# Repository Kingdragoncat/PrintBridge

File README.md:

# PrintBridge

Im so done with needing to unplug all my cords and plug it all in ontip of a file of boxes to print one god damn thing so i made my wired printer wireless

## what is this thing

A small, cheap PCB that turns a wired USB printer into a WiFi network printer. It plugs into the printer's USB port as a USB **Host**, and exposes it on the network via raw JetDirect (port 9100) printing — works natively with macOS/Windows/Linux print dialogs, no drivers needed on the printer side.

Print jobs get spooled to the onboard micro SD card first, so if your wifi drops mid-print the job is safe and keeps going. because my wifi used to be *that* bad.

## pcb layout

## schematic

## specs

- ESP32-S3-WROOM-1 module — WiFi + native USB Host on one chip
- USB-A host port to connect to the printer
- USB-C for power input (5V only, no data)
- Micro SD card slot for print job spooling
- WS2812B addressable RGB status LED
- BOOT and RESET tactile switches
- 1x4 UART header for firmware flashing (with an external USB-serial adapter)
- AMS1117-3.3 voltage regulator with polyfuse protection
- FCC/CE modular certification inherited from the WROOM-1 module
- Board size: ~55 x 28mm

## how it works

1. plug PrintBridge into your printer's USB port
2. power it with any USB-C charger
3. it connects to your WiFi and starts listening on port 9100
4. add it as a network printer on your computer (raw/JetDirect protocol)
5. print! the job gets spooled to the SD card first, then fed to the printer

## wiring

**USB-C power in (J2):** 5V power only, no data lines connected. CC1/CC2 have 5.1k pull-downs so any USB-C charger recognizes it as a power sink. goes through a polyfuse for overcurrent protection, then into the AMS1117-3.3 regulator.

**USB-A host (USB1):** D+ and D- are wired to the ESP32-S3's USB PHY (GPIO19/GPIO20). VBUS gets raw 5V from the power rail — host mode has to supply power to the printer.

**SD card (J1):** SPI connection to the ESP32-S3 for spooling print data before sending to the printer.

**Status LED (D1):** WS2812B addressable LED. blue=booting, yellow=connecting, green=ready, cyan=receiving, purple=printing, red=error.

**Flashing:** no onboard USB-serial chip to keep costs down. use an external ~$3 USB-to-UART dongle on the 4-pin UART header (J3: 3V3/GND/TX/RX).

## BOM

every part has an LCSC part number and link so anyone can source and build this.

| Ref | Qty | Value | LCSC # | Package | Description | Unit Price | Subtotal | Link |
|-----|-----|-------|--------|---------|-------------|------------|----------|------|
| U1 | 1 | ESP32-S3-WROOM-1-N8 | C2913198 | Module | ESP32-S3 WiFi/BLE module (8MB flash) | $2.88 | $2.88 | [LCSC](https://www.lcsc.com/product-detail/C2913198.html) |
| USB1 | 1 | USB-A-F-90 | C168708 | Through-hole | USB-A host receptacle (to printer) | $0.15 | $0.15 | [LCSC](https://www.lcsc.com/product-detail/C168708.html) |
| J2 | 1 | TYPE-C-31-M-12 | C165948 | SMD | USB-C power input | $0.10 | $0.10 | [LCSC](https://www.lcsc.com/product-detail/C165948.html) |
| U2 | 1 | AMS1117-3.3 | C6186 | SOT-223 | 3.3V linear regulator | $0.05 | $0.05 | [LCSC](https://www.lcsc.com/product-detail/C6186.html) |
| SW1, SW2 | 2 | TS-1187A-B-A-B | C318884 | SMD | Tactile switches (BOOT + RESET) | $0.02 | $0.04 | [LCSC](https://www.lcsc.com/product-detail/C318884.html) |
| J1 | 1 | DM3AT-SF-PEJM5 | C114218 | SMD | Micro SD card connector | $0.65 | $0.65 | [LCSC](https://www.lcsc.com/product-detail/C114218.html) |
| D1 | 1 | WS2812B | C2761795 | 5050 | Addressable RGB status LED | $0.08 | $0.08 | [LCSC](https://www.lcsc.com/product-detail/C2761795.html) |
| R1, R2 | 2 | 10k | C269742 | 0805 | Pull-up resistors (EN + BOOT) | $0.01 | $0.02 | [LCSC](https://www.lcsc.com/product-detail/C269742.html) |
| R3, R4 | 2 | 5.1k | C269748 | 0805 | USB-C CC pull-down resistors | $0.01 | $0.02 | [LCSC](https://www.lcsc.com/product-detail/C269748.html) |
| C1, C3 | 2 | 100nF | C38141 | 0805 | Decoupling capacitors | $0.01 | $0.02 | [LCSC](https://www.lcsc.com/product-detail/C38141.html) |
| C2 | 1 | 10uF | C92341 | 0805 | Bulk capacitor (3V3 rail) | $0.02 | $0.02 | [LCSC](https://www.lcsc.com/product-detail/C92341.html) |
| C4 | 1 | 10uF | C92341 | 0805 | Bulk capacitor (SD card) | $0.02 | $0.02 | [LCSC](https://www.lcsc.com/product-detail/C92341.html) |
| F1 | 1 | Polyfuse 500mA | C106264 | 1206 | PTC resettable fuse | $0.07 | $0.07 | [LCSC](https://www.lcsc.com/product-detail/C106264.html) |
| J3 | 1 | Conn_01x04 | — | 2.54mm | UART pin header (for flashing) | $0.05 | $0.05 | [LCSC](https://www.lcsc.com/search?q=1x4+2.54mm+pin+header) |

**total: 18 parts — ~$4.17**

## firmware

the firmware is in the `software/` folder. its a PlatformIO project (Arduino framework). wifi, SD spooling, and the TCP print server are working. USB host printer driver is WIP.

see [software/README.md](software/README.md) for build and flash instructions.

## references

- [Espressif KiCad Libraries](https://github.com/espressif/kicad-libraries) — official symbols, footprints, 3D models
- [ESP32S3_PrintServer](https://github.com/MAXXTANG/ESP32S3_PrintServer) — reference firmware for ESP32-S3 print bridge
- [EspUsbHost](https://github.com/tanakamasayuki/EspUsbHost) — Arduino USB Host library for ESP32-S3

## license

do whatever you want with it honestly

---

made by Jonah Novoseller (Kingdragoncat)

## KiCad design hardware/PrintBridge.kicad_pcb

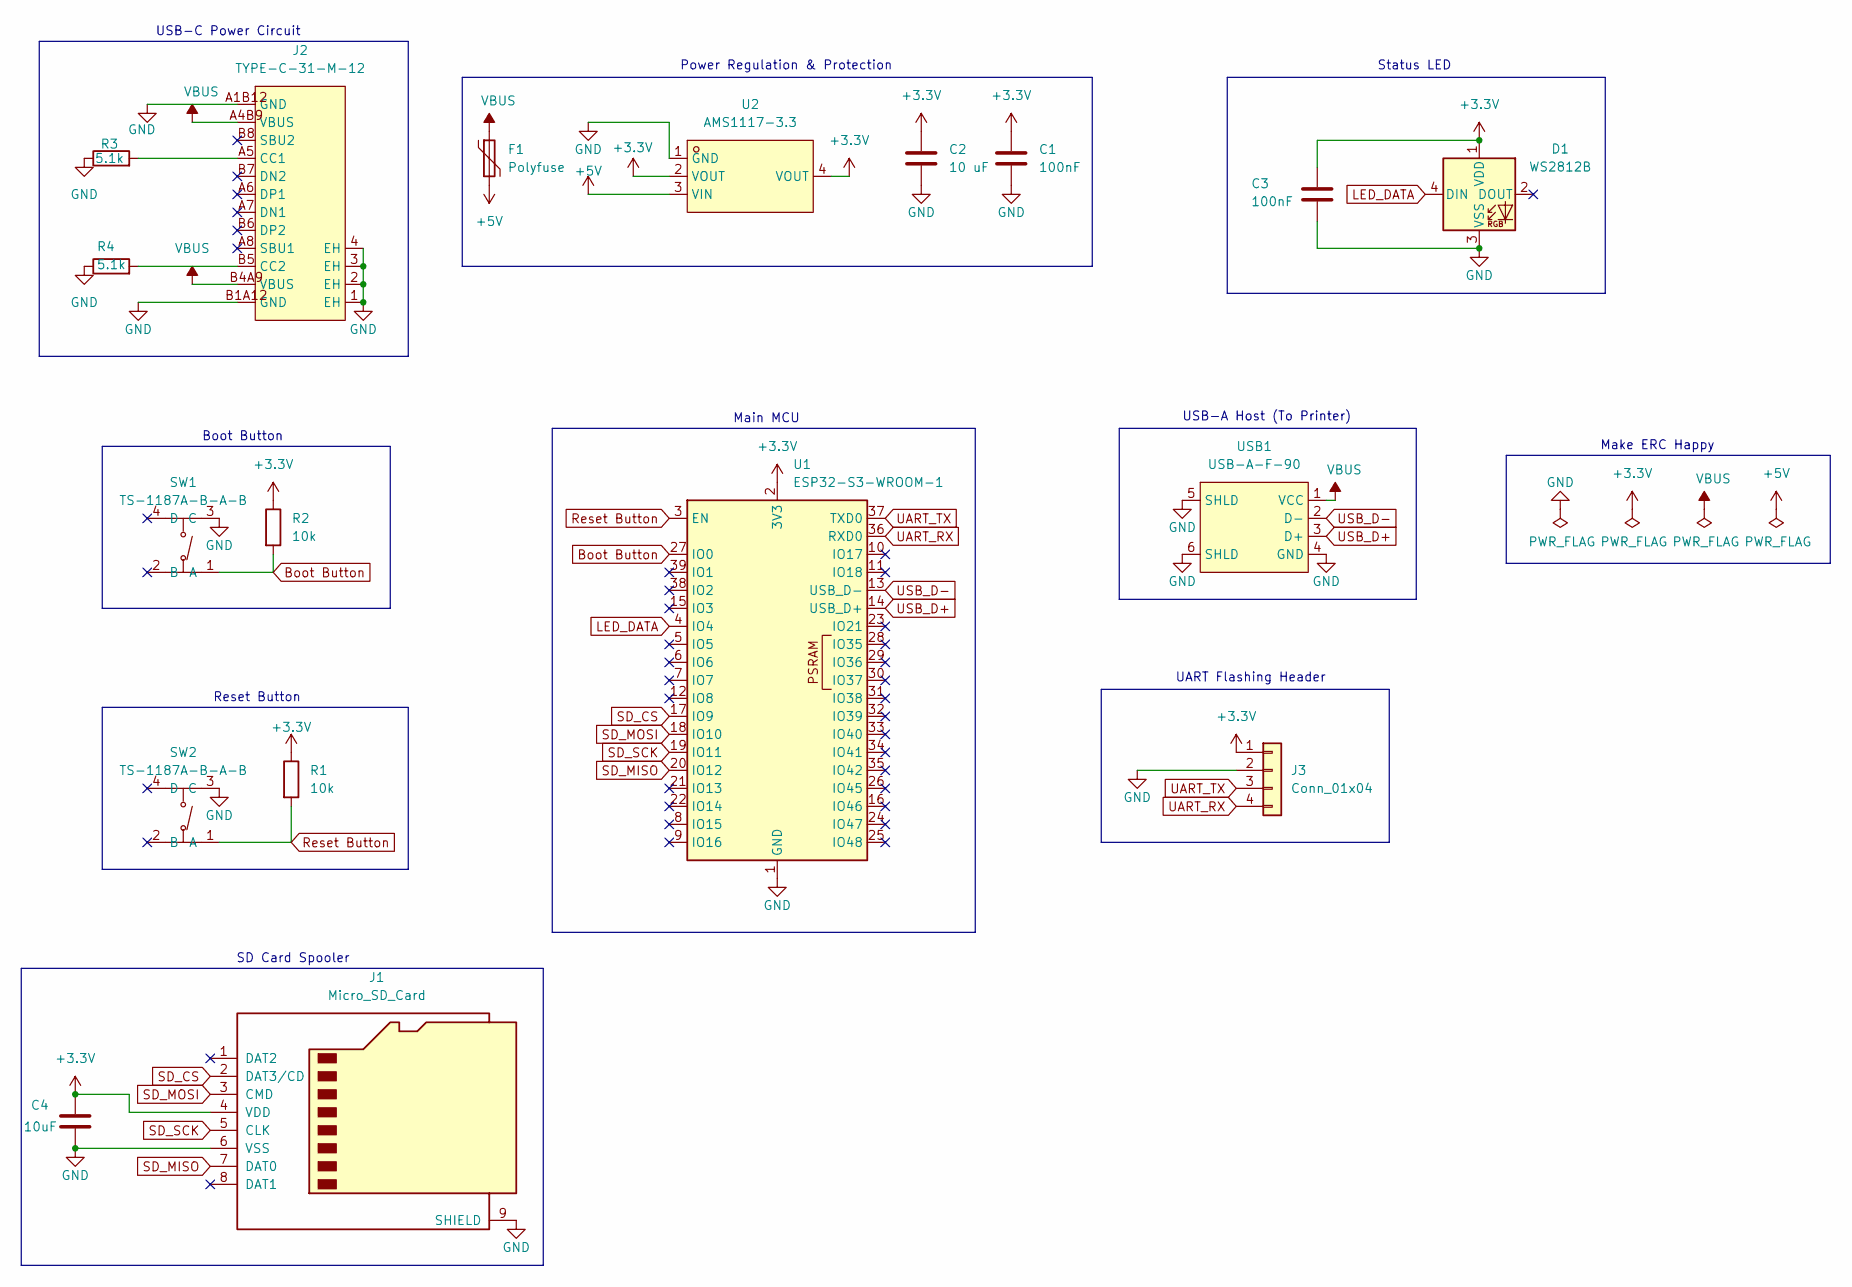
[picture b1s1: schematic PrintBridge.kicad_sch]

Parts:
C1, C3: 100nF; C_0805_2012Metric_Pad1.18x1.45mm_HandSolder
C2: 10 uF; C_0805_2012Metric_Pad1.18x1.45mm_HandSolder
C4: 10uF; C_0805_2012Metric_Pad1.18x1.45mm_HandSolder
D1: WS2812B; LED_WS2812B_PLCC4_5.0x5.0mm_P3.2mm
F1: Polyfuse; Fuse_1206_3216Metric_Pad1.42x1.75mm_HandSolder
J1: Micro_SD_Card; microSD_HC_Hirose_DM3AT-SF-PEJM5
J2: TYPE-C-31-M-12; USB-C_SMD-TYPE-C-31-M-12_1; MPN TYPE-C-31-M-12; LCSC Part C165948
J3: Conn_01x04; PinSocket_1x04_P2.54mm_Vertical
R1, R2: 10k; R_0805_2012Metric_Pad1.20x1.40mm_HandSolder
R3, R4: 5.1k; R_0805_2012Metric_Pad1.20x1.40mm_HandSolder
SW1, SW2: TS-1187A-B-A-B; SW-SMD_4P-L5.1-W5.1-P3.70-LS6.5-TL_H1.5; MPN TS-1187A-B-A-B; LCSC Part C318884
U1: ESP32-S3-WROOM-1
U2: AMS1117-3.3; SOT-223-3_L6.5-W3.4-P2.30-LS7.0-BR; MPN AMS1117-3.3; LCSC Part C6186
USB1: USB-A-F-90; USB-A-TH_C168708; MPN A/F90度外扣铜壳鱼叉脚无卷边加高9.3白胶PBT 不耐高温; LCSC Part C168708

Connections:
+3.3V: C1.1, C2.1, C3.1, C4.1, D1.1 (VDD), J1.4 (VDD), J3.1, R1.1, R2.1, U1.2 (3V3), U2.2 (VOUT), U2.4 (VOUT)
+5V: F1.2, U2.3 (VIN)
Boot Button: R2.2, SW1.1 (A), U1.27 (IO0)
GND: C1.2, C2.2, C3.2, C4.2, D1.3 (VSS), J1.6 (VSS), J1.9 (SHIELD), J2.1 (EH), J2.2 (EH), J2.3 (EH), J2.4 (EH), J2.A1B12 (GND), J2.B1A12 (GND), J3.2, R3.1, R4.1, SW1.3 (C), SW2.3 (C), U1.1 (GND), U1.40 (GND), U1.41 (GND), U2.1 (GND), USB1.4 (GND), USB1.5 (SHLD), USB1.6 (SHLD)
LED_DATA: D1.4 (DIN), U1.4 (IO4)
unnamed: J2.A5 (CC1), R3.2
unnamed: J2.B5 (CC2), R4.2
Reset Button: R1.2, SW2.1 (A), U1.3 (EN)
SD_CS: J1.2 (DAT3/CD), U1.17 (IO9)
SD_MISO: J1.7 (DAT0), U1.20 (IO12)
SD_MOSI: J1.3 (CMD), U1.18 (IO10)
SD_SCK: J1.5 (CLK), U1.19 (IO11)
UART_RX: J3.4, U1.36 (RXD0)
UART_TX: J3.3, U1.37 (TXD0)
USB_D+: U1.14 (USB_D+), USB1.3 (D+)
USB_D-: U1.13 (USB_D-), USB1.2 (D-)
VBUS: F1.1, J2.A4B9 (VBUS), J2.B4A9 (VBUS), USB1.1 (VCC)

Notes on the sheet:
Reset Button
UART Flashing Header
Boot Button
SD Card Spooler
Main MCU
Power Regulation & Protection
Status LED
USB-A Host (To Printer)
Make ERC Happy
USB-C Power Circuit

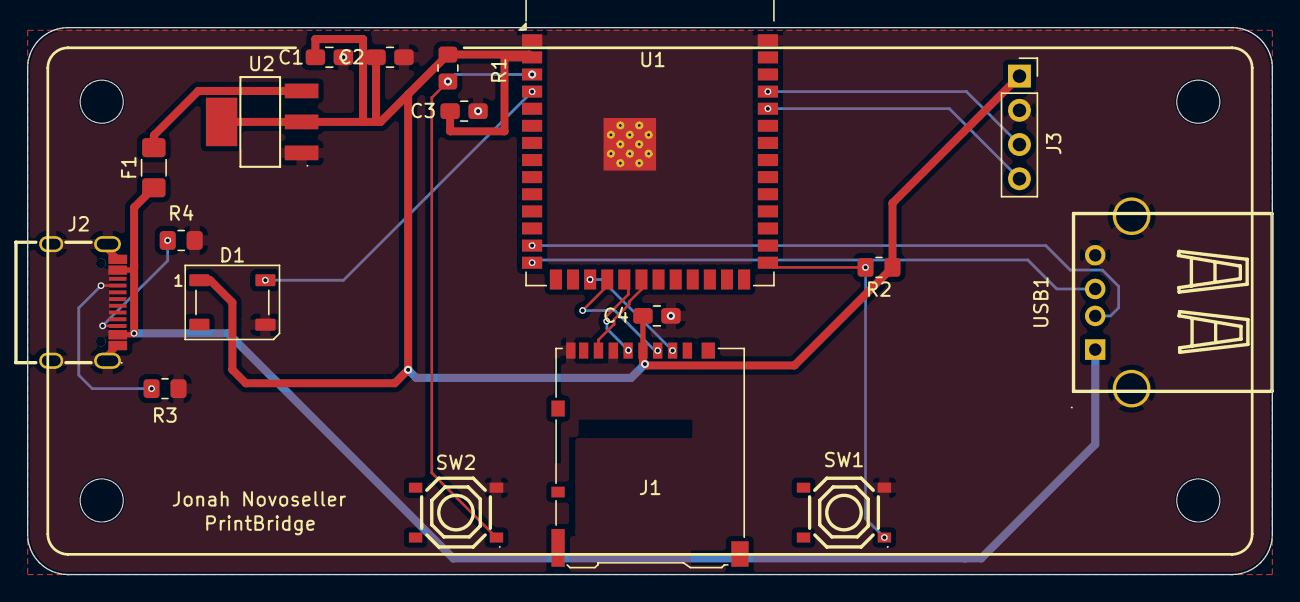
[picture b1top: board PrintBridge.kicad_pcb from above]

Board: 2 copper layers, 92.4 x 40.6 mm, 18 parts (0 on the bottom side), 17 nets.

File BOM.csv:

Reference,Qty,Value,LCSC Part #,Package,Description,Unit Price,Subtotal,Link
"U1",1,ESP32-S3-WROOM-1-N8,C2913198,Module,ESP32-S3 WiFi/BLE module (8MB flash),$2.88,$2.88,https://www.lcsc.com/product-detail/C2913198.html
"USB1",1,USB-A-F-90,C168708,Through-hole,USB-A host receptacle (to printer),$0.15,$0.15,https://www.lcsc.com/product-detail/C168708.html
"J2",1,TYPE-C-31-M-12,C165948,SMD,USB-C power input (5V only),$0.10,$0.10,https://www.lcsc.com/product-detail/C165948.html
"U2",1,AMS1117-3.3,C6186,SOT-223,3.3V linear regulator,$0.05,$0.05,https://www.lcsc.com/product-detail/C6186.html
"SW1, SW2",2,TS-1187A-B-A-B,C318884,SMD,Tactile switch (BOOT + RESET),$0.02,$0.04,https://www.lcsc.com/product-detail/C318884.html
"J1",1,Micro_SD_Card (DM3AT-SF-PEJM5),C114218,SMD,Micro SD card connector,$0.65,$0.65,https://www.lcsc.com/product-detail/C114218.html
"D1",1,WS2812B,C2761795,5050,Addressable RGB status LED,$0.08,$0.08,https://www.lcsc.com/product-detail/C2761795.html
"R1, R2",2,10k,C269742,0805,Pull-up resistors (EN + BOOT),$0.01,$0.02,https://www.lcsc.com/product-detail/C269742.html
"R3, R4",2,5.1k,C269748,0805,USB-C CC1/CC2 pull-down resistors,$0.01,$0.02,https://www.lcsc.com/product-detail/C269748.html
"C1, C3",2,100nF,C38141,0805,Ceramic decoupling capacitors,$0.01,$0.02,https://www.lcsc.com/product-detail/C38141.html
"C2",1,10uF,C92341,0805,Ceramic bulk capacitor (3V3 rail),$0.02,$0.02,https://www.lcsc.com/product-detail/C92341.html
"C4",1,10uF,C92341,0805,Ceramic bulk capacitor (SD card),$0.02,$0.02,https://www.lcsc.com/product-detail/C92341.html
"F1",1,Polyfuse 500mA,C106264,1206,PTC resettable fuse (USB-C 5V in),$0.07,$0.07,https://www.lcsc.com/product-detail/C106264.html
"J3",1,Conn_01x04,—,2.54mm,UART pin header (for flashing),$0.05,$0.05,https://www.lcsc.com/search?q=1x4+2.54mm+pin+header
,,,,,,,,
,,,,,"TOTAL (18 parts)",,"$4.17",

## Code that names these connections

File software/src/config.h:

#pragma once
#ifndef CONFIG_H
#define CONFIG_H

// If config.local.h exists, use private user credentials (git-ignored)
#if __has_include("config.local.h")
#include "config.local.h"
#else

// ---- WiFi Credentials ----
#define WIFI_SSID     "YOUR_WIFI_SSID"
#define WIFI_PASSWORD "YOUR_WIFI_PASSWORD"

// ---- Static IP Configuration (Optional) ----
#define USE_STATIC_IP false
#define STATIC_IP      192, 168, 1, 50
#define STATIC_GATEWAY 192, 168, 1, 1
#define STATIC_SUBNET  255, 255, 255, 0
#define STATIC_DNS     192, 168, 1, 1

#endif

// ---- Network ----
#define PRINT_PORT 9100 // raw TCP / JetDirect

// ---- Hardware Pins (ESP32-S3 custom PCB) ----
// USB host D+/D- are handled internally by the S3's USB PHY (GPIO19/20)

// Status LED (WS2812B)
#define LED_DATA_PIN 4 // Pin IO4 on schematic
#define NUM_LEDS 1

// MicroSD Card (SPI)
#define SD_CS 9    // Pin IO9 on schematic
#define SD_MOSI 10 // Pin IO10 on schematic
#define SD_SCK 11  // Pin IO11 on schematic
#define SD_MISO 12 // Pin IO12 on schematic

// UART is on default U0 pins (TX=43, RX=44)

#endif
